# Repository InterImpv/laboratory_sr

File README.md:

# laboratory_sr
4labs from university

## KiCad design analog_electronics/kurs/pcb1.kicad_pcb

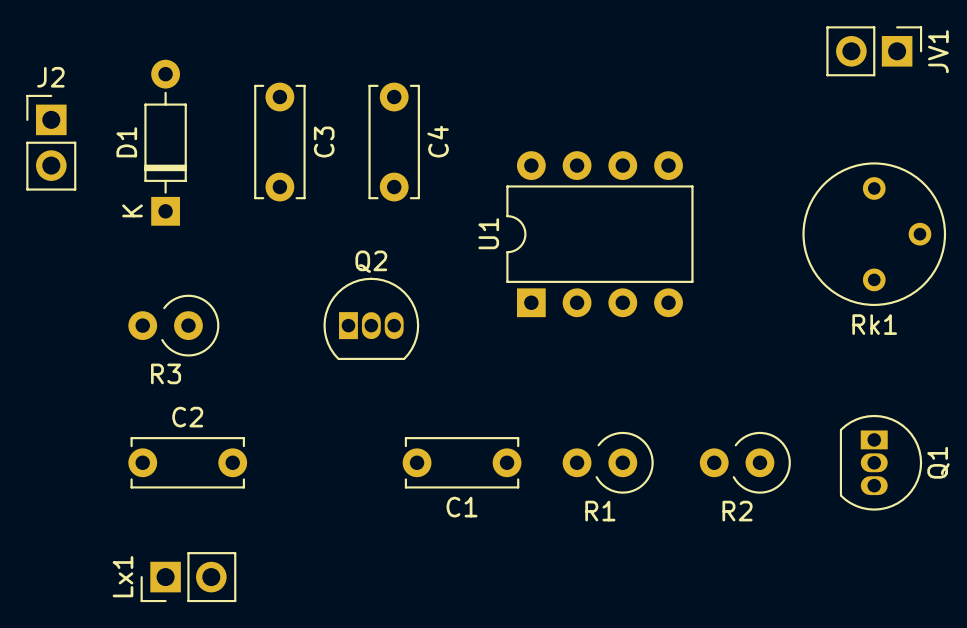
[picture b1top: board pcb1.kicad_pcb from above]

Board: 2 copper layers, 15 parts (0 on the bottom side), 10 nets, no tracks yet.

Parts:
C1: 100n; C_Disc_D6.0mm_W2.5mm_P5.00mm
C2, C4: 10n; C_Disc_D6.0mm_W2.5mm_P5.00mm
C3: 10u; C_Disc_D6.0mm_W2.5mm_P5.00mm
D1: 1N4148; D_DO-35_SOD27_P7.62mm_Horizontal
J2: Amp; PinHeader_1x02_P2.54mm_Vertical
JV1: Vcc; PinHeader_1x02_P2.54mm_Vertical
Lx1: L; PinHeader_1x02_P2.54mm_Vertical
Q1, Q2: BC547; TO-92_Inline
R1: 1k; R_Axial_DIN0309_L9.0mm_D3.2mm_P2.54mm_Vertical
R2: 4.7k; R_Axial_DIN0309_L9.0mm_D3.2mm_P2.54mm_Vertical
R3: 160k; R_Axial_DIN0309_L9.0mm_D3.2mm_P2.54mm_Vertical
Rk1: R_POT; Potentiometer_Bourns_3339P_Vertical
U1: LM555xN; DIP-8_W7.62mm

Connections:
GND: C1.2, C2.2, C4.2, JV1.2, Lx1.2, Q2.3, U1.1
unnamed: C1.1, R1.2, U1.2, U1.6
unnamed: C2.1, Lx1.1, Q1.3, R3.2
unnamed: C3.1, D1.2, J2.1, JV1.1, Rk1.1, Rk1.2, U1.8
unnamed: C3.2, D1.1, J2.2, Q2.1
unnamed: C4.1, U1.5
unnamed: Q1.1, Rk1.3
unnamed: Q1.2, R2.1
unnamed: Q2.2, R3.1
unnamed: R1.1, R2.2, U1.3

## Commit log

2020-04-13 an_lr.01_13.04.2020
2020-04-14 updated analog_lab #1 and uploaded otk_lab #1
2020-04-21 updated otk_lab #1 and uploaded analog_lab #2
2020-04-23 updated otk_lr1 and an_lr1, uploaded otk_lr2, otk_lr3
2020-04-23 forgot about an_lr1
2020-04-29 updated otk_lr5 and it's measurements
2020-05-06 added otk_lr6 and updated an_lr2
2020-05-19 updated otk_lr7
2020-05-20 updated otk_lr_7, fixed a very awkward error
2020-06-01 better late than never
2020-06-02 slight adjustments
2020-12-21 added new thing for masm stuff
2020-12-21 uploaded pdfs
2022-02-07 haphazard commit
2022-02-08 rewrote everything as i wanted
2022-02-14 final version of lab1
